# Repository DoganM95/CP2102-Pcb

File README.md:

# Recreated test board

<table>
  <tr>
    <td></td>
    <td></td>
  </tr>
</table>

# Aliexpress module  
<table>
  <tr>
    <td></td>
    <td></td>
  </tr>
</table>

## Repository contains:

- Photoshop project
- Autodesk EAGLE schematic

## Pcb measures:

- Width: 21,5 mm
- Height: 16 mm
- Thickness: 1,15 mm (without components)

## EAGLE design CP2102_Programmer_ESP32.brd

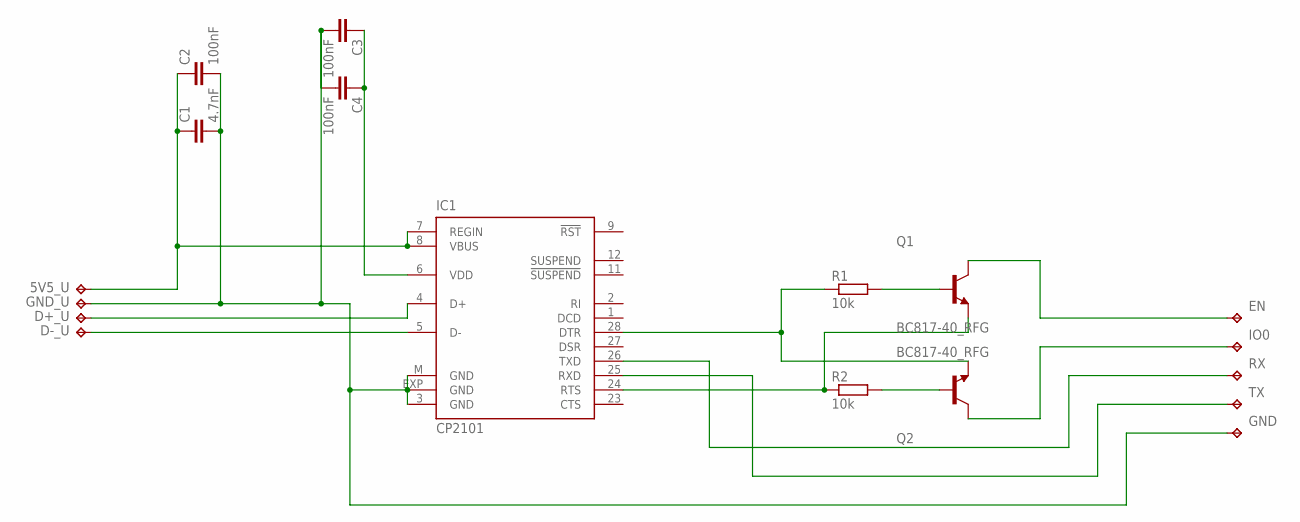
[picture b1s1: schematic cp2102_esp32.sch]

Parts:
5V5_U: TPB1,27; B1,27
C1: 4.7nF; C0603
C2, C3, C4: 100nF; C0603
D+_U: TPB1,27; B1,27
D-_U: TPB1,27; B1,27
EN: TPB1,27; B1,27
GND: TPB1,27; B1,27
GND_U: TPB1,27; B1,27
IC1: CP2101; MLP28
IO0: TPB1,27; B1,27
Q1, Q2: BC817-40_RFG; SOT95P237X112-3N
R1, R2: 10k; R0603
RX: TPB1,27; B1,27
TX: TPB1,27; B1,27

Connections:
unnamed: C3.1, C4.1, IC1.6 (VDD)
unnamed: IC1.26 (TXD), RX.TP
unnamed: IC1.25 (RXD), TX.TP
unnamed: D+_U.TP, IC1.4 (D+)
unnamed: D-_U.TP, IC1.5 (D-)
unnamed: IC1.28 (DTR), Q2.2 (E), R1.1
unnamed: 5V5_U.TP, C1.1, C2.1, IC1.7 (REGIN), IC1.8 (VBUS)
unnamed: IC1.24 (RTS), Q1.2 (E), R2.1
unnamed: C1.2, C2.2, C3.2, C4.2, GND.TP, GND_U.TP, IC1.3 (GND), IC1.EXP (GND), IC1.M (GND)
unnamed: IO0.TP, Q2.3 (C)
unnamed: Q2.1 (B), R2.2
unnamed: Q1.1 (B), R1.2
unnamed: EN.TP, Q1.3 (C)

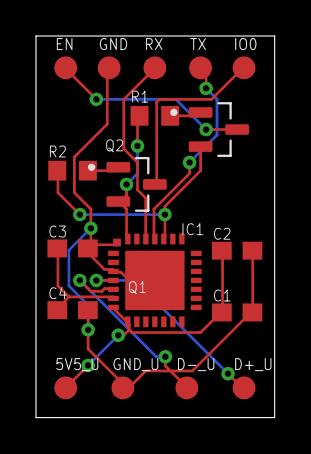
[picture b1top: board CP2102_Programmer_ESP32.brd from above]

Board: 2 copper layers, 13.3 x 21.2 mm, 18 parts (0 on the bottom side), 13 nets.

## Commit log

2023-05-06 add reversed files
2023-05-06 add description
2023-05-06 fix markdown issues
2023-05-06 add measures
2023-05-06 add pic
2023-11-10 add ignore
2023-11-10 restructure & add recreated variant
2023-11-10 restructure again
2023-11-10 renaming
2023-11-10 add previews
2023-11-10 more restructuring
2023-11-10 restructure
